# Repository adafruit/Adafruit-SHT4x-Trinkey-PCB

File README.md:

## Adafruit SHT4x Trinkey - USB Temperature and Humidity Sensor PCB

<a href="http://www.adafruit.com/products/5896"><br/>
Click here to purchase one from the Adafruit shop</a><br>
<a href="http://www.adafruit.com/products/5912"><br/>
Click here to purchase one from the Adafruit shop</a>

PCB files for the Adafruit SHT4x Trinkey - USB Temperature and Humidity Sensor. 

Format is EagleCAD schematic and board layout
* https://www.adafruit.com/product/5896
* https://www.adafruit.com/product/5912

### Description

It's half USB Key, half temperature-humidity sensor... it's the Adafruit SHT4x Trinkey. We wanted to make it super-easy to add one of our most popular combination environmental sensors to any computer with a USB A port.

The PCB is designed to slip into any USB A port on a computer or laptop. There's an ATSAMD21 microcontroller on board with just enough circuitry to keep it happy. One pin of the microcontroller connects to a NeoPixel LED. Another pin is used as a capacitive touch input on the end. A reset button lets you enter bootloader mode if necessary. That's it!

The SAMD21 can run CircuitPython or Arduino very nicely - both have existing SHT4x, NeoPixel, and our FreeTouch (capacitive touch) libraries. Over the USB connection, you can have serial, MIDI, or HID connectivity.

There are two versions of this Trinkey: the SHT45 and the SHT41. Sensirion Temperature/Humidity sensors are some of the finest and highest-accuracy devices you can get. The SHT45 sensor is the fourth generation (started at the SHT10 and worked its way up to the top!). The SHT45 has an excellent ±1.0% typical relative humidity accuracy from 25 to 75% and ±0.1°C typical accuracy from 0 to 75 °C. Note that the reported temperature may be a few degrees higher than ambient due to self-heating.

The SHT41 sensor is the fourth generation of I2C temperature and humidity sensor from Sensirion. (They started at the SHT10 and reached the top!). The SHT41 has an excellent ±1.8% typical relative humidity accuracy from 25 to 75% and ±0.2 °C typical accuracy from 0 to 75 °C. Note that the reported temperature may be a few degrees higher than ambient due to self-heating.

The SHT4x Trinkey is perfect for simple projects that want to read the ambient temperature and humidity without extra wiring, soldering, drivers, or complex software. We even ship the board pre-programmed with code that will print a unique serial number, the temperature, humidity, and touch sensor over a serial/COM port in CSV (comma separated value) format, so you can use it immediately.  If you need to measure farther than the computer port, simply use any USB A extension cable.

We think it's just an adorable little board. It's small, durable, and inexpensive enough that it could be a first microcontroller board or inspiration for advanced developers to make something simple and fun.

* ATSAMD21E18 32-bit Cortex M0+ - 48 MHz 32 bit processor with 256KB Flash and 32 KB RAM
* Native USB supported by every OS - can be used in Arduino or CircuitPython as USB serial console, MIDI, Keyboard/Mouse HID, even a little disk drive for storing Python scripts.
* Can be used with Arduino IDE or CircuitPython
* One RGB NeoPixel LED
* One Capacitive Touchpad
* SHT4x Temperature + Humidity sensor with thermal-isolation cutout
* Reset switch for starting your project code over or entering bootloader mode
* Slim and cute, keychain-friendly!

### License

Adafruit invests time and resources providing this open source design, please support Adafruit and open-source hardware by purchasing products from [Adafruit](https://www.adafruit.com)!

Designed by Limor Fried/Ladyada for Adafruit Industries.

Creative Commons Attribution/Share-Alike, all text above must be included in any redistribution. 
See license.txt for additional details.

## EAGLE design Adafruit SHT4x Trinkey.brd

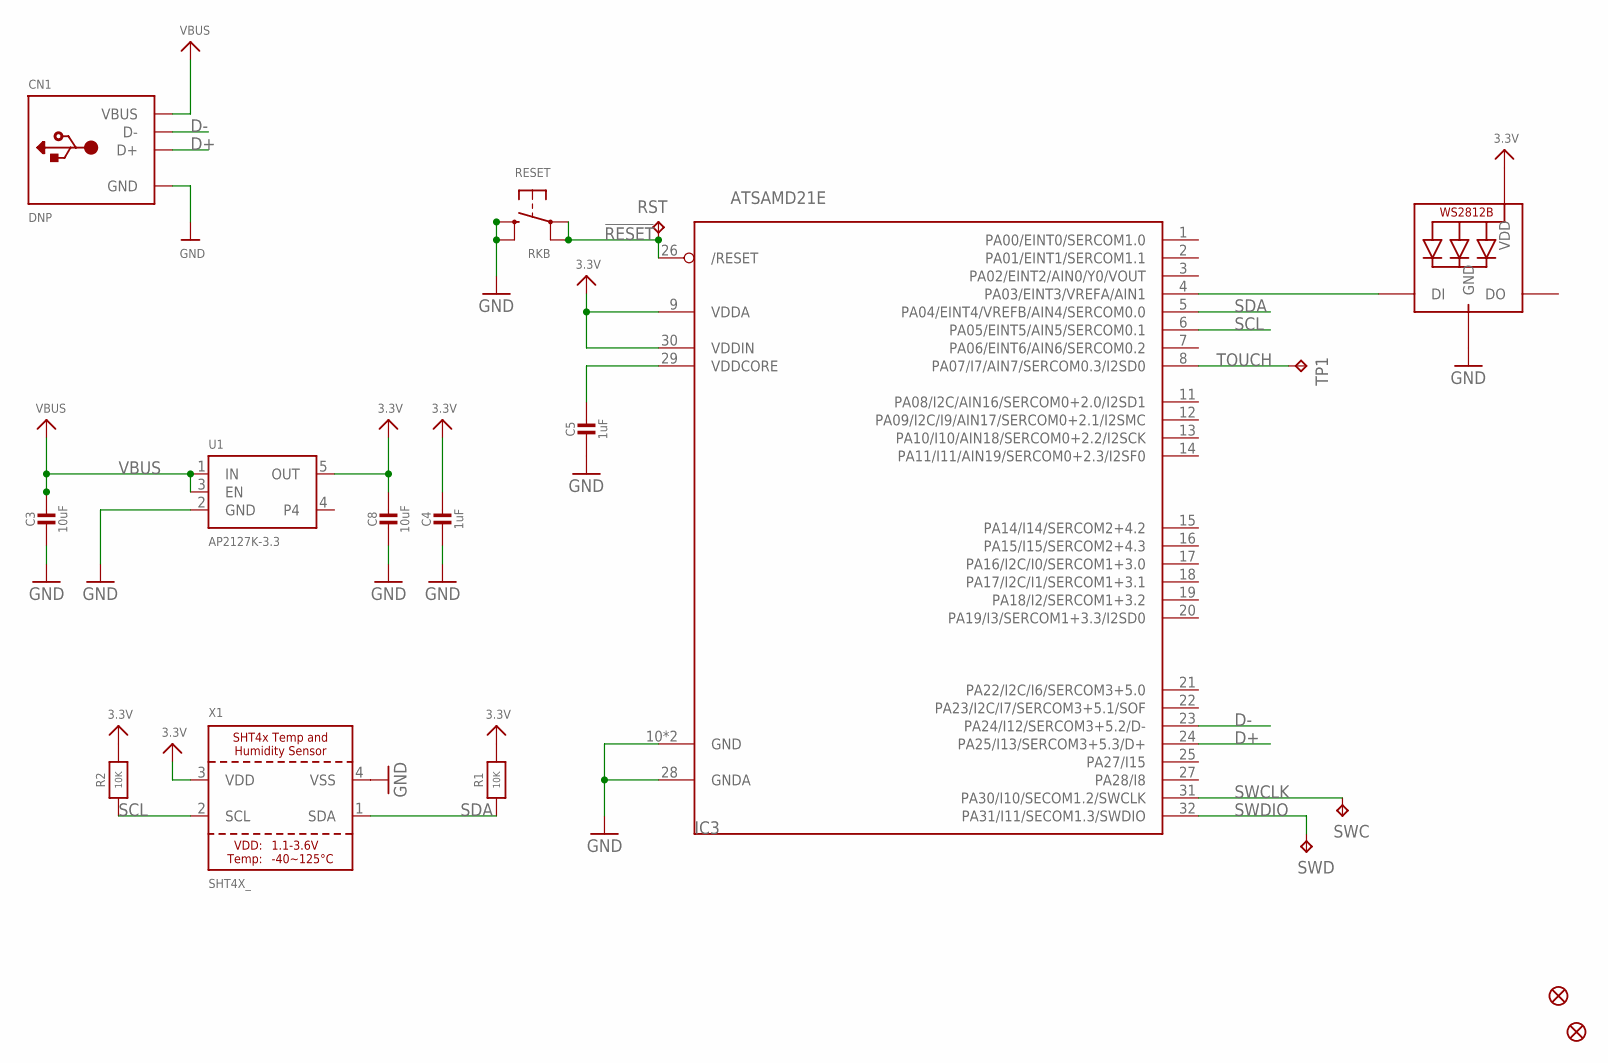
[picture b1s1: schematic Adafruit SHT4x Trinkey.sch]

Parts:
C3, C8: 10uF; 0805-NO
C4: 1uF; _0603MP
C5: 1uF; 0603-NO
CN1: DNP; USBA_PCB
FID1, FID2: FIDUCIAL_0.5MM
IC3: ATSAMD21E; QFN32_5MM
LED1: WS2812B_SK6805_1515; SK6805_1515
R1, R2: 10K; _0402NO
RESET: RKB; BTN_RKB2_4.6X2.8
RST: TPTP16R; TP16R
SWC: TPTP15R; TP15R
SWD: TPTP16R; TP16R
TP1: DNP; TP13R
U1: AP2127K-3.3; SOT23-5; JLC_ROTATION 0
X1: SHT4X_; SHT4X

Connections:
3.3V: C4.1, C8.1, IC3.9 (VDDA), IC3.30 (VDDIN), LED1.2 (VDD), R1.2, R2.2, U1.5 (OUT), X1.3 (VDD)
!RESET: IC3.26 (/RESET), RESET.A, RESET.A' (P1), RST.TP
D+: CN1.USB_PLUS (D+), IC3.24 (PA25/I13/SERCOM3+5.3/D+)
D-: CN1.USB_NEG (D-), IC3.23 (PA24/I12/SERCOM3+5.2/D-)
GND: C3.2, C4.2, C5.2, C8.2, CN1.GND, IC3.10 (GND), IC3.28 (GNDA), IC3.33 (GND), LED1.4 (GND), RESET.B (S), RESET.B' (S1), U1.2 (GND), X1.4 (VSS)
unnamed: IC3.4 (PA03/EINT3/VREFA/AIN1), LED1.1 (DI)
SCL: IC3.6 (PA05/EINT5/AIN5/SERCOM0.1), R2.1, X1.2 (SCL)
SDA: IC3.5 (PA04/EINT4/VREFB/AIN4/SERCOM0.0), R1.1, X1.1 (SDA)
SWCLK: IC3.31 (PA30/I10/SECOM1.2/SWCLK), SWC.TP
SWDIO: IC3.32 (PA31/I11/SECOM1.3/SWDIO), SWD.TP
TOUCH: IC3.8 (PA07/I7/AIN7/SERCOM0.3/I2SD0), TP1.TP
VBUS: C3.1, CN1.VCC (VBUS), U1.1 (IN), U1.3 (EN)
VDDCORE1: C5.1, IC3.29 (VDDCORE)

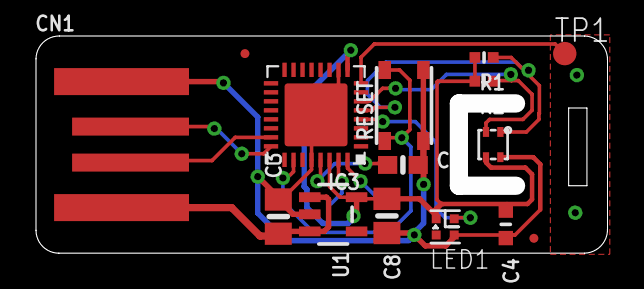
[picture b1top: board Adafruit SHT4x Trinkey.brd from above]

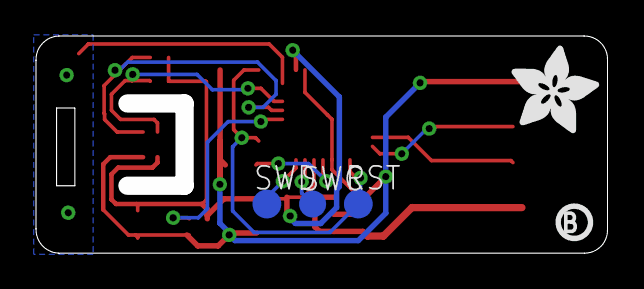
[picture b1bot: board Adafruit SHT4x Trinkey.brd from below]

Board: 2 copper layers, 30.7 x 11.0 mm, 28 parts (9 on the bottom side), 13 nets.

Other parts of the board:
PLABEL4: PLABEL4
PLABEL5: PLABEL5
PLABEL6: PLABEL6
PLABEL7: PLABEL7
PLABEL8: PLABEL8
PLABEL9: PLABEL9
PLABEL10: PLABEL10
PLABEL11: PLABEL11
U$7: ADAFRUIT_5MM
U$8: PCBFEAT-REV-040

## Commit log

2024-03-22 cookiecutter
2024-03-26 prettypins
2024-03-26 factory reset UF2
2024-03-27 add arduino pins
2024-03-27 category order

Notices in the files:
parts and their libraries:
microbuilder: This work is placed in the public domain, and may be freely used for commercial and non-commercial work with the following conditions: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
